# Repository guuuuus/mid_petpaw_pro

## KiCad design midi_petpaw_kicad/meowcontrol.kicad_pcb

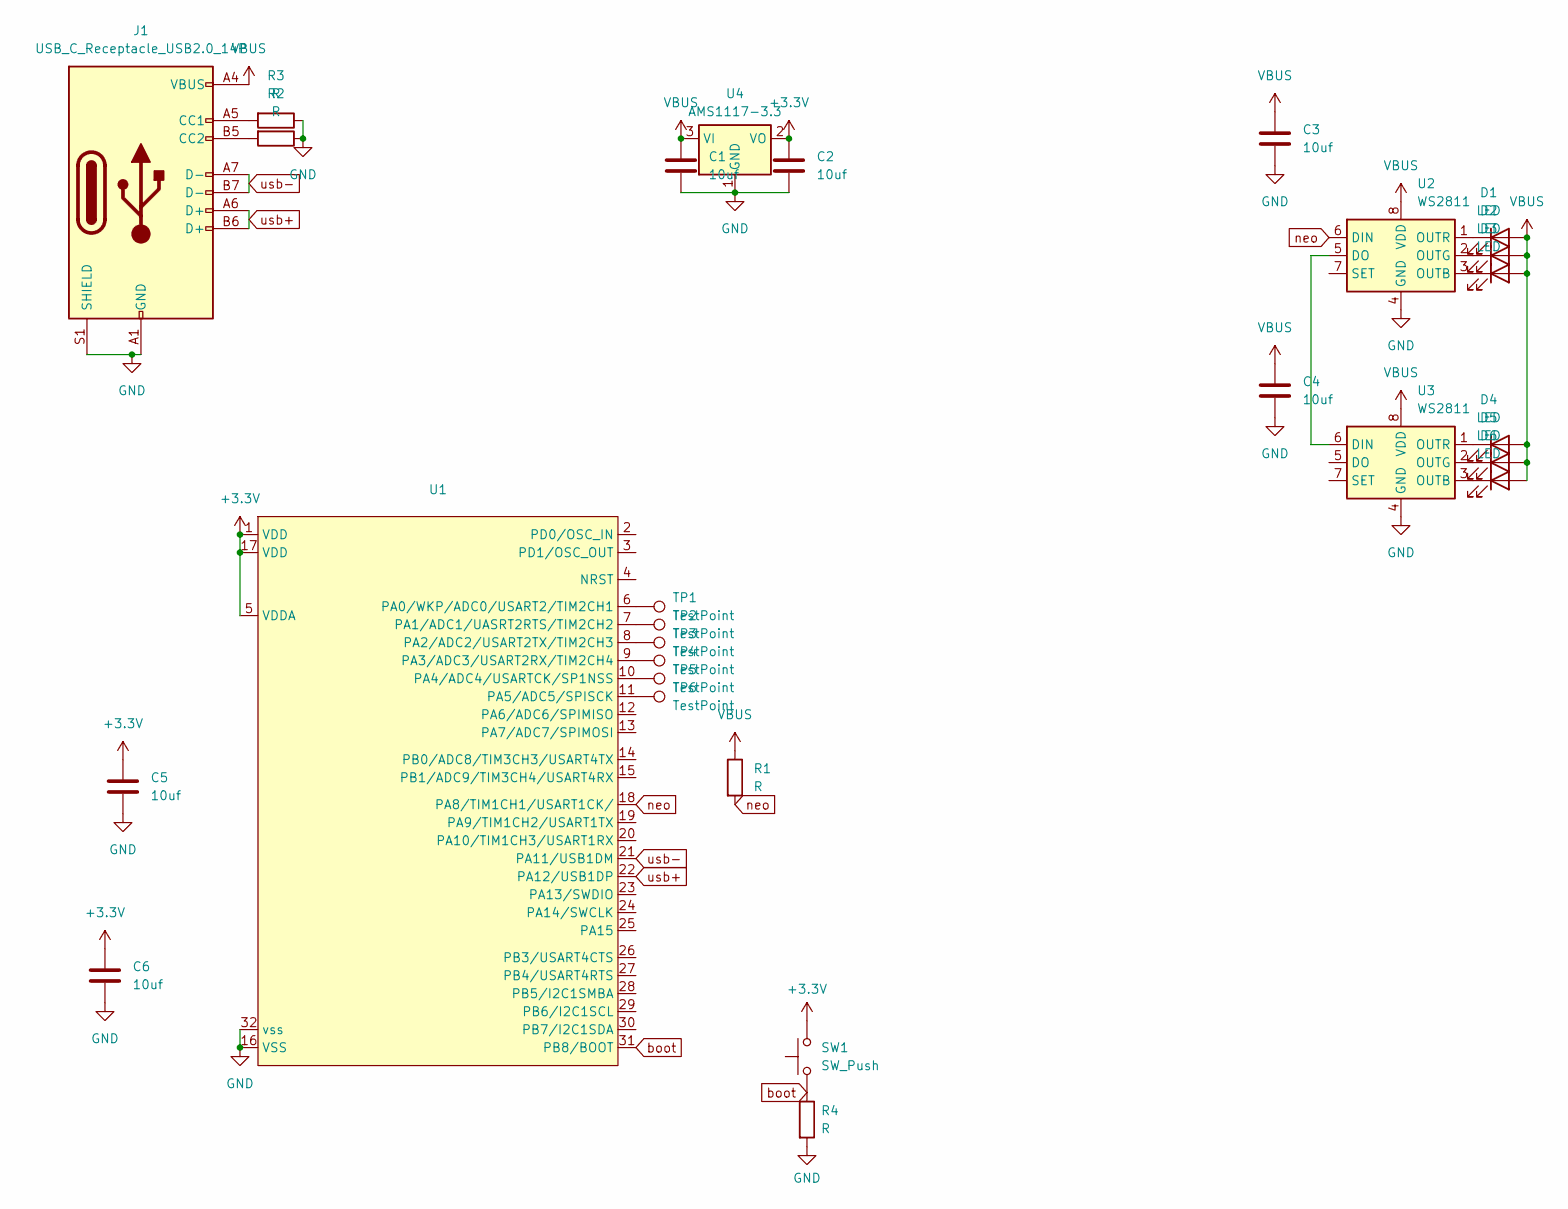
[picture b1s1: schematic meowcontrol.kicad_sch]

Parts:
C1, C2, C3, C4, C5, C6: 10uf; C_1206_3216Metric_Pad1.33x1.80mm_HandSolder
D1, D2, D3, D4, D5, D6: LED; LED_1206_3216Metric_Pad1.42x1.75mm_HandSolder
J1: USB_C_Receptacle_USB2.0_14P; USB_C_Receptacle_GCT_USB4105-xx-A_16P_TopMnt_Horizontal
R1, R2, R3, R4: R; R_1206_3216Metric_Pad1.30x1.75mm_HandSolder
SW1: SW_Push; SW_PUSH_6mm
TP1, TP2, TP3, TP4, TP5, TP6: TestPoint; TestPoint_Pad_1.0x1.0mm_W_SOLDERMASK
U1: LQFP-32_7x7mm_P0.8mm
U2, U3: WS2811; SO-8_3.9x4.9mm_P1.27mm
U4: AMS1117-3.3; SOT-223-3_TabPin2

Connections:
+3.3V: C2.1, C5.1, C6.1, SW1.2, U1.1 (VDD), U1.5 (VDDA), U1.17 (VDD), U4.2 (VO)
GND: C1.2, C2.2, C3.2, C4.2, C5.2, C6.2, J1.A1 (GND), J1.A12 (GND), J1.B1 (GND), J1.B12 (GND), J1.S1 (SHIELD), R2.1, R3.1, R4.2, U1.16 (VSS), U1.32 (vss), U2.4 (GND), U3.4 (GND), U4.1 (GND)
unnamed: D1.1 (K), U2.1 (OUTR)
unnamed: D2.1 (K), U2.2 (OUTG)
unnamed: D3.1 (K), U2.3 (OUTB)
unnamed: D4.1 (K), U3.1 (OUTR)
unnamed: D5.1 (K), U3.2 (OUTG)
unnamed: D6.1 (K), U3.3 (OUTB)
unnamed: J1.A5 (CC1), R3.2
unnamed: J1.B5 (CC2), R2.2
unnamed: TP1.1, U1.6 (PA0/WKP/ADC0/USART2/TIM2CH1)
unnamed: TP2.1, U1.7 (PA1/ADC1/UASRT2RTS/TIM2CH2)
unnamed: TP3.1, U1.8 (PA2/ADC2/USART2TX/TIM2CH3)
unnamed: TP4.1, U1.9 (PA3/ADC3/USART2RX/TIM2CH4)
unnamed: TP5.1, U1.10 (PA4/ADC4/USARTCK/SP1NSS)
unnamed: TP6.1, U1.11 (PA5/ADC5/SPISCK)
unnamed: U2.5 (DO), U3.6 (DIN)
VBUS: C1.1, C3.1, C4.1, D1.2 (A), D2.2 (A), D3.2 (A), D4.2 (A), D5.2 (A), D6.2 (A), J1.A4 (VBUS), J1.A9 (VBUS), J1.B4 (VBUS), J1.B9 (VBUS), R1.1, U2.8 (VDD), U3.8 (VDD), U4.3 (VI)
boot: R4.1, SW1.1, U1.31 (PB8/BOOT)
neo: R1.2, U1.18 (PA8/TIM1CH1/USART1CK/), U2.6 (DIN)
usb+: J1.A6 (D+), J1.B6 (D+), U1.22 (PA12/USB1DP)
usb-: J1.A7 (D-), J1.B7 (D-), U1.21 (PA11/USB1DM)

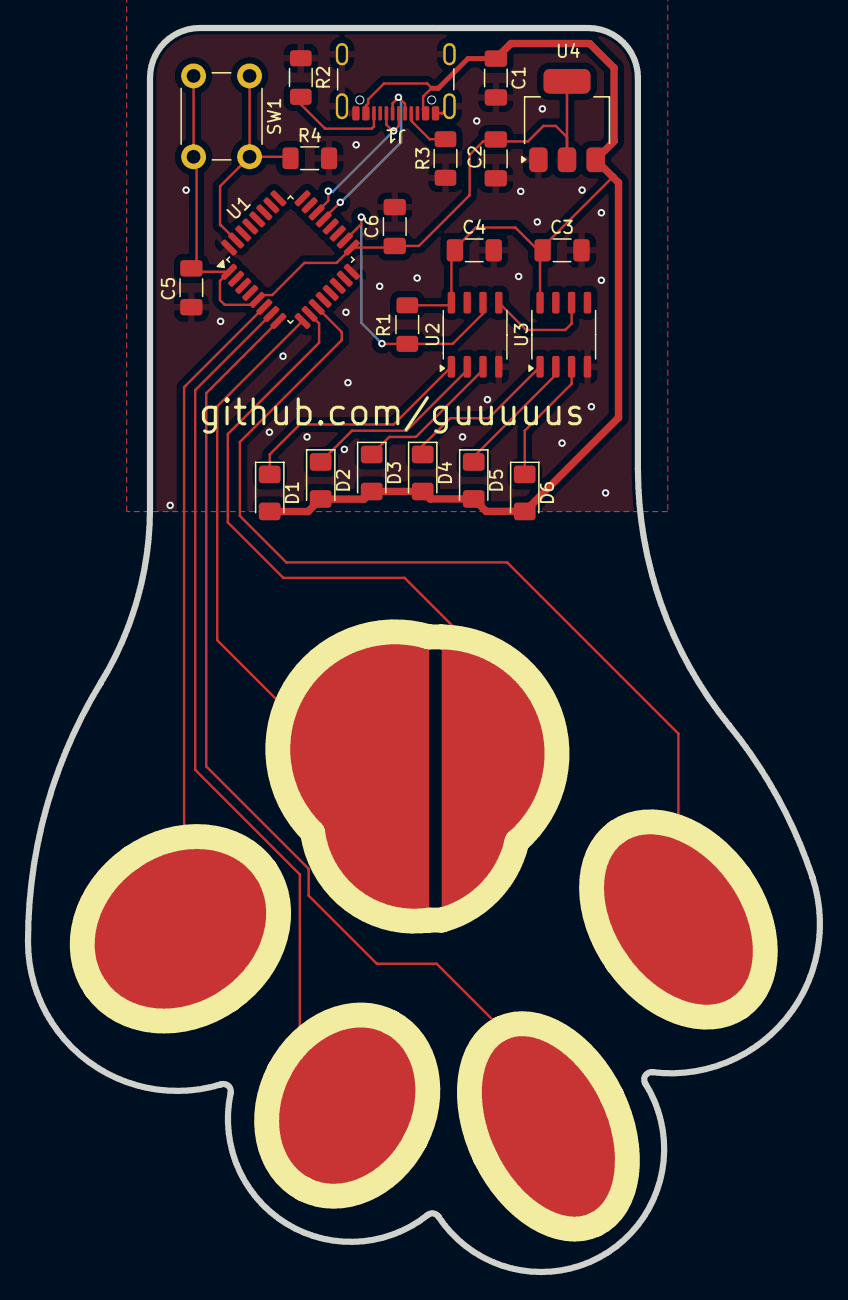
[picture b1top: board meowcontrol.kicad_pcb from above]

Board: 2 copper layers, 63.7 x 100.0 mm, 28 parts (0 on the bottom side), 22 nets.

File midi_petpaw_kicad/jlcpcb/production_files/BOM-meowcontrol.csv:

Comment,Designator,Footprint,LCSC
TestPoint,TP6,TestPoint_Pad_1.0x1.0mm_W_SOLDERMASK,
TestPoint,TP5,TestPoint_Pad_1.0x1.0mm_W_SOLDERMASK,
TestPoint,TP4,TestPoint_Pad_1.0x1.0mm_W_SOLDERMASK,
TestPoint,TP3,TestPoint_Pad_1.0x1.0mm_W_SOLDERMASK,
TestPoint,TP2,TestPoint_Pad_1.0x1.0mm_W_SOLDERMASK,
TestPoint,TP1,TestPoint_Pad_1.0x1.0mm_W_SOLDERMASK,
R,R4,R_1206_3216Metric_Pad1.30x1.75mm_HandSolder,
SW_Push,SW1,SW_PUSH_6mm,
LED,D6,LED_1206_3216Metric_Pad1.42x1.75mm_HandSolder,
LED,D5,LED_1206_3216Metric_Pad1.42x1.75mm_HandSolder,
LED,D4,LED_1206_3216Metric_Pad1.42x1.75mm_HandSolder,
LED,D3,LED_1206_3216Metric_Pad1.42x1.75mm_HandSolder,
LED,D2,LED_1206_3216Metric_Pad1.42x1.75mm_HandSolder,
LED,D1,LED_1206_3216Metric_Pad1.42x1.75mm_HandSolder,
10uf,C6,C_1206_3216Metric_Pad1.33x1.80mm_HandSolder,
AMS1117-3.3,U4,SOT-223-3_TabPin2,
WS2811,U3,SO-8_3.9x4.9mm_P1.27mm,
WS2811,U2,SO-8_3.9x4.9mm_P1.27mm,
~,U1,LQFP-32_7x7mm_P0.8mm,
R,R3,R_1206_3216Metric_Pad1.30x1.75mm_HandSolder,
R,R2,R_1206_3216Metric_Pad1.30x1.75mm_HandSolder,
R,R1,R_1206_3216Metric_Pad1.30x1.75mm_HandSolder,
USB_C_Receptacle_USB2.0_14P,J1,USB_C_Receptacle_GCT_USB4105-xx-A_16P_TopMnt_Horizontal,
10uf,C5,C_1206_3216Metric_Pad1.33x1.80mm_HandSolder,
10uf,C4,C_1206_3216Metric_Pad1.33x1.80mm_HandSolder,
10uf,C3,C_1206_3216Metric_Pad1.33x1.80mm_HandSolder,
10uf,C2,C_1206_3216Metric_Pad1.33x1.80mm_HandSolder,
10uf,C1,C_1206_3216Metric_Pad1.33x1.80mm_HandSolder,

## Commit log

2024-09-28 toggle
2024-09-28 kicad files
